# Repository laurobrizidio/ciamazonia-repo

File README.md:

# CI Amazonia - Curso de Microeletrônica

## Repositórios Internos

- [Unidade 1 - Básico de Linux para Projetos Eletrônicos](unid01_fund_linux/)
- [Unidade 2 - Fundamentos de Eletrônica Digital](unid02_fundeletronicadigital/)
  - [Simulações LTspice](unid02_fundeletronicadigital/ltspice_simulations/)
- [Unidade 3 - Fundamentos de CMOS / LTspice](unid03_ltspice/)
- [Unidade 4 - KiCad e VLSI](unid04_kicad/)
  - [Projeto NOR Gate](unid04_kicad/norgate/)
- [Unidade 5 - Design Digital / UNICASS](unid05_unicass/)
  - [Atividade 01](unid05_unicass/atv01/)
  - [MUX 4:1](unid05_unicass/atv01/mux4/)
  - [Aula 06/03 - Somador](unid05_unicass/aula0603/)
  - [Atividade 02](unid05_unicass/atv02/)
- [Projeto Final - Array SRAM 6T 4x4](projetofinal/)

## Conteúdo Programático

## Unidade 1 – Básico de Linux para Projetos Eletrônicos (3 semanas)

- Conceitos fundamentais do sistema operacional Linux.
- Estrutura de diretórios, permissões de arquivos e comandos essenciais do terminal.
- Edição de arquivos (vim, nano, gedit) e criação de scripts Bash.
- Redirecionamentos, pipes e automação de tarefas.
- Instalação e gerenciamento de pacotes (apt, yum).
- Variáveis de ambiente e arquivos de configuração de shell (.bashrc, .profile).
- Manipulação de logs e depuração de erros.
- Introdução a Makefiles e uso básico do Git em projetos HDL.
- Fundamentos do Yocto Project: BitBake, Poky e layers.
- Setup do ambiente de build e criação de camadas customizadas.
- Definição de recipes para pacotes e imagens.
- Customização de kernel, rootfs e construção de imagens mínimas (QEMU/Raspberry Pi).
- Debug e deploy da imagem gerada.

## Unidade 2 – Fundamentos de Eletrônica Digital (2 semanas)

- Álgebra booleana e simplificação de expressões lógicas.
- Portas lógicas básicas e compostas (AND, OR, NOT, NAND, XOR).
- Conceitos de flip-flops, registradores, contadores e multiplexadores.
- Aplicações de circuitos combinacionais e sequenciais.

## Unidade 3 – Fundamentos de CMOS (3 semanas)

- Estrutura de cristais semicondutores (Si, Ge, GaAs).
- Diodos e transistores de efeito de campo (JFET, MOSFET).
- Tipos de MOSFET: depleção e intensificação.
- Curvas características e comportamento elétrico.
- Lógica CMOS: evolução (SSI a VLSI) e Lei de Moore.
- Projeto de inversores e portas NAND/NOR em CMOS.
- Portas compostas, transistores de passagem, tristates e multiplexadores.

## Unidade 4 – VLSI e Very Deep Sub Micron (4 semanas)

- Introdução ao layout CMOS e processo de fabricação em wafer.
- Regras de design (MOSIS), stick diagrams e layout de portas.
- Etapas de fabricação: formação do wafer, poços, fotolitografia, isolamento, gate, dreno, contatos, metalização e passivação.
- Noções de metrologia e técnicas de medição.
- Regras de projeto: wells, transistores, contatos, vias e metal.
- Tecnologias avançadas: SOI, dielétricos high-k/low-k, silício tensionado, transistores plásticos e de alta tensão.
- Melhorias de processo: FinFETs e nanotubos de carbono.
- Design for Manufacturability (DFM) e problemas de fabricação.
- Efeitos parasitas, calibração, migração de tecnologia e tapeout de circuitos integrados.

## Unidade 5 – Design Digital

- Introdução à linguagem HDL (SystemVerilog): modelagem comportamental e estrutural.
- Simulação lógica e análise temporal básica.
- Projeto hierárquico de sistemas digitais.
- FSM (máquinas de estado finito): Mealy e Moore.
- Considerações de clock, setup/hold, skew e race condition.
- Introdução a teoria de grafos.
- BDD, ROBDDs, STAMINA e NOVA.

## Unidade 6 – Otimização do processo CMOS (VLSI)

- Delay: Otimização de tempo, Resposta do transiente, RC delay model, impacto do layout na capacitância, Modelo de atraso linear, Esforço Lógico, Parasitic delay.
- Potência: Potência dinâmica e estática, clock gating, glitches, DVFS em SoCs, corrente de curto-circuito, subthreshold (DIBL) e gate leakage, BTBT e GIDL, multi-VDD e otimização do atraso-energia.
- Interconexões: Geometria dos fios, modelagem de interconexões (resistência, capacitância, indutância, skin effect e temperatura), delay, controle de crosstalk, ruído, repetidores e regeneradores
- Robustez: Variabilidade: Tensão de Alimentação, Temperatura, Variação do processo, Design corners; Confiabilidade: Terminologia de Confiabilidade, Desgaste do Óxido, Desgaste das Interconexões, Erros Suaves, Falha por Sobretensão, Latchup; Escalonamento: Escalonamento de Transistores, Escalonamento de Interconexões, Roteiro Tecnológico Internacional para Semicondutores, Impactos no Projeto.

## Unidade 7 - Fluxo de projeto ASIC

- Design Flow: Evolução, era da integração, ferramentas incrementais, acesso esparso e desafios futuros.
- Síntese lógica: síntese RTL, minimização em 2 e múltiplos níveis, modelagem de biblioteca, análise de tempo (STA) e síntese física.
- Análise e Otimização de Potência do Nível de Circuito ao Nível RTL: análise de potência, Redução de Consumo no nível de circuito e síntese lógica para baixa potência.
- Verificação de Equivalência: lógica booleana aplicada, verificação de equivalência Combinacional e sequencial.
- Alocação de Células (placement) no Layout Digital: etapa global de posicionamento, Refinamento do Placement e Correção Legal e Avanços Recentes em Técnicas de Placement.
- Análise Estática de Tempo (STA): Modelos de Atraso em Níveis Lógicos, Verificação de Atrasos em Lógica Combinacional, Análise de Tempo em Circuitos Sequenciais e sob variações.
- Roteamento: Técnicas de roteamento simples e multinet, análise de congestionamento, atraso e slew, roteamento de clock e estratégias modernas de interconexão.
- Gate Sizing: Modelos de atraso e algoritmos práticos.
- Projeto e Síntese de Clock: Distribuição de clock global/local e técnicas de low power.
- Design closure: Evolução do fluxo de projeto e restrições de design (econômicas, de desempenho, potência e confiabilidade), práticas atuais desde o RTL até o roteamento, e otimizações finais incluindo CTS e variabilidade.
- Design Rule Check: Operações de DRC, DRC Baseado em Linguagem, Projeto para Fabricação, Reconhecimento de Padrões, Multipadrões.
- Design for Manufacturability (DFM): Modelagem de perdas de rendimento, otimizações lógicas e paramétricas, simulações estatísticas e integração da fabricabilidade ao fluxo de síntese física.
- Extração de Layout: análise de problemas, extração de dispositivos projetados e parasitários, conectividade, resistência, capacitância e indutância, além de redução de rede e variações de processo.
- Introdução aos principais EDA tools (Synopsys, ChipInventor, Cadence, Mentor).

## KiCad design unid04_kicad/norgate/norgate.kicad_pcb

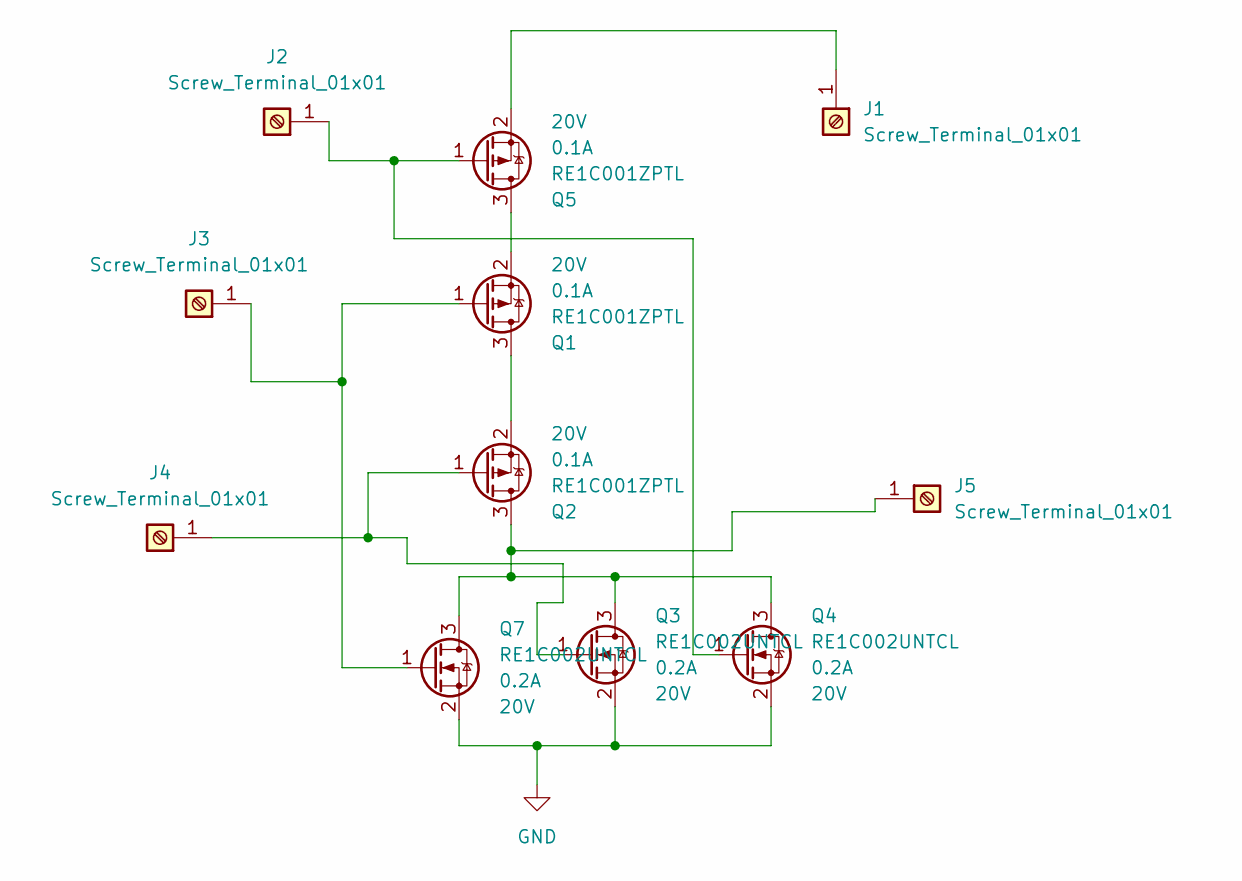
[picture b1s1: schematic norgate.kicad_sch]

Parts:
J1, J2, J3, J4, J5: Screw_Terminal_01x01; TerminalBlock_MetzConnect_360271_1x01_Horizontal_ScrewM3.0_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
Q1, Q2, Q5: RE1C001ZPTL; SC-89 SOT-490
Q3, Q4, Q7: RE1C002UNTCL; SC-89 SOT-490

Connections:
GND: Q3.2 (S), Q4.2 (S), Q7.2 (S)
unnamed: J1.1, Q5.2 (S)
unnamed: J2.1, Q4.1 (G), Q5.1 (G)
unnamed: J3.1, Q1.1 (G), Q7.1 (G)
unnamed: J4.1, Q2.1 (G), Q3.1 (G)
unnamed: J5.1, Q2.3 (D), Q3.3 (D), Q4.3 (D), Q7.3 (D)
unnamed: Q1.3 (D), Q2.2 (S)
unnamed: Q1.2 (S), Q5.3 (D)

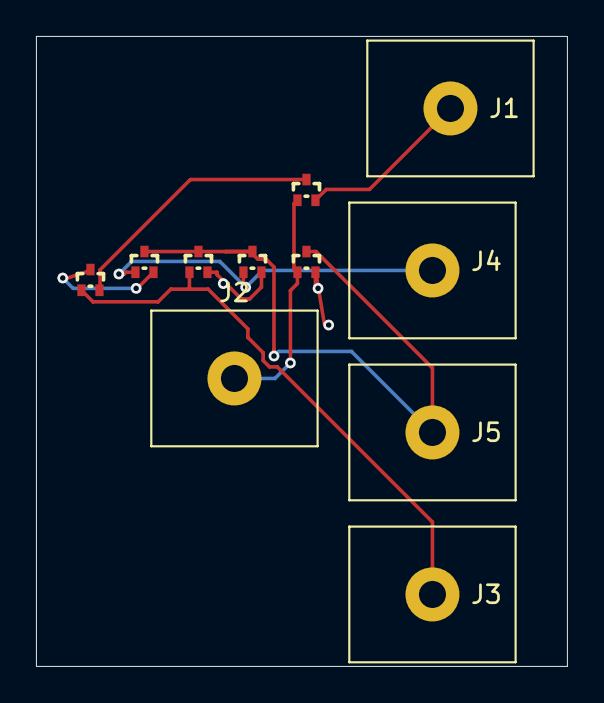
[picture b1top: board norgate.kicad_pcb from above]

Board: 2 copper layers, 29.5 x 35.0 mm, 11 parts (0 on the bottom side), 8 nets.

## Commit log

2025-12-08 Primeiro commit
2025-12-08 Add Makefile
2026-03-04 Added files of simulations
2026-03-04 Added lt_spice simulations
2026-03-05 Kicad nor gate project
2026-03-06 added unid05 unicass
2026-03-06 Aula 01 - 06032026 Prof.Andre
2026-03-07 Added .gitignore
2026-03-08 Added config.yaml into mux_4_to_1 ckt
2026-06-03 docs: update repository readmes
2026-06-03 chore: add remaining project files
2026-06-03 chore: add shared final project files
2026-06-19 docs: add project final design diagrams
2026-06-19 docs: add markdown reports for linux fundamentals
2026-06-19 docs: add mux activity README
2026-06-19 docs: add unicass activity READMEs
2026-06-19 docs: rename unicass activity folders
